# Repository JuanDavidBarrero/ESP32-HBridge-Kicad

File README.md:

# ESP32-HBridge-Kicad
 PCB EPS32 Hbridge

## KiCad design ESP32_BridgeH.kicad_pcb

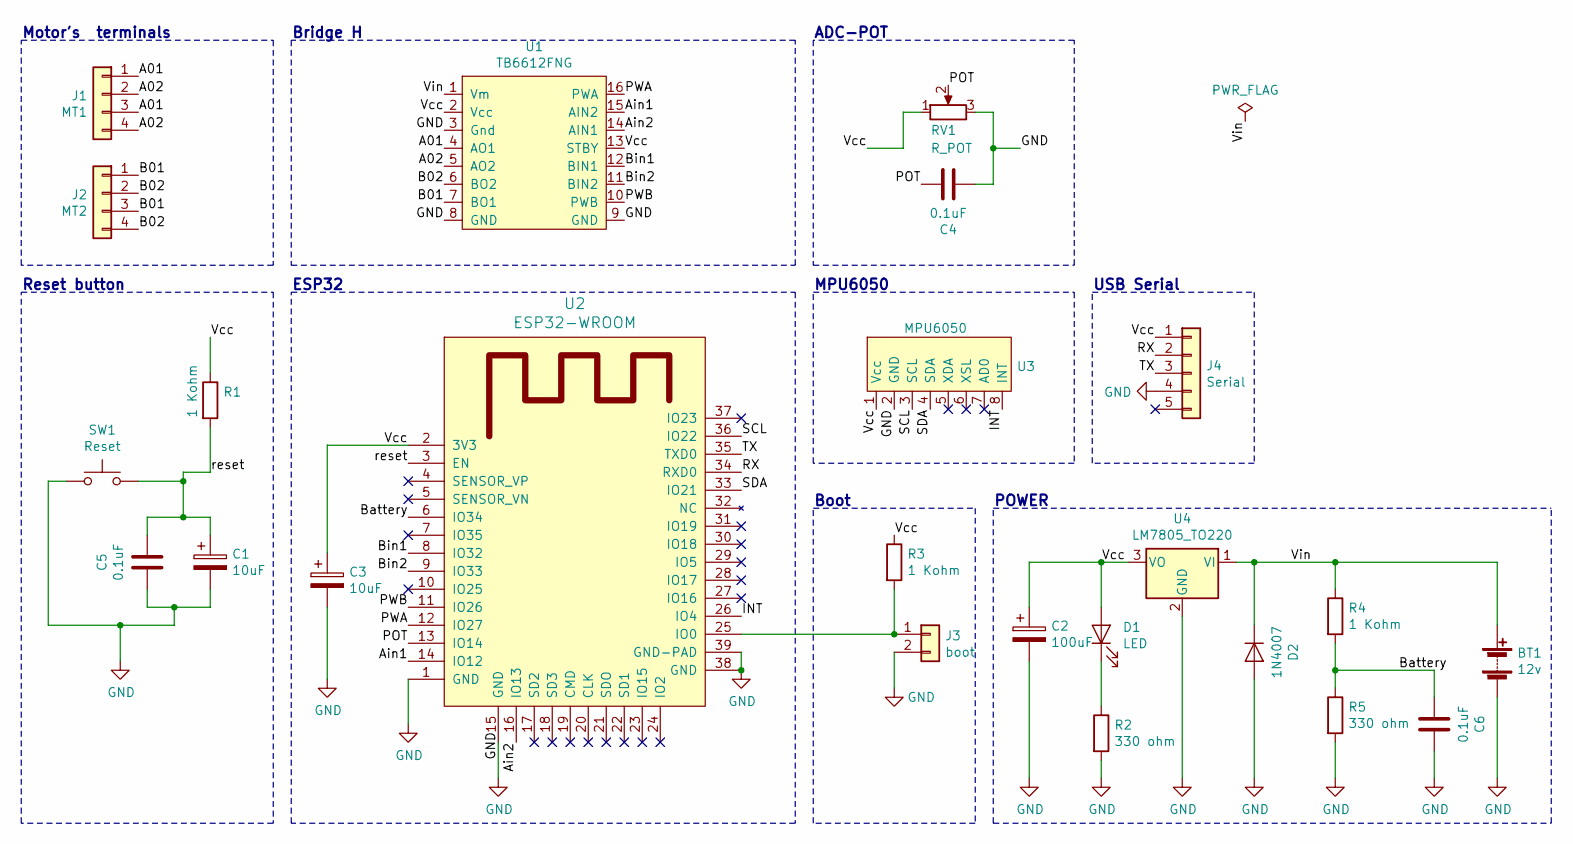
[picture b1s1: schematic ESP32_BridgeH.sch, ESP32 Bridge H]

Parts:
BT1: 12v; TerminalBlock_bornier-2_P5.08mm
C1, C3: 10uF; CP_Radial_D5.0mm_P2.50mm
C2: 100uF; CP_Radial_D8.0mm_P3.50mm
C4, C5, C6: 0.1uF; C_Disc_D4.3mm_W1.9mm_P5.00mm
D1: LED; LED_D5.0mm
D2: 1N4007; D_DO-41_SOD81_P10.16mm_Horizontal
J1: MT1; TerminalBlock_bornier-4_P5.08mm
J2: MT2; TerminalBlock_bornier-4_P5.08mm
J3: boot; PinHeader_1x02_P2.54mm_Vertical
J4: Serial; PinSocket_1x05_P2.54mm_Vertical
R1: 1 Kohm; R_Axial_DIN0207_L6.3mm_D2.5mm_P7.62mm_Horizontal
R2: 330 ohm; R_Axial_DIN0207_L6.3mm_D2.5mm_P7.62mm_Horizontal
R3, R4: 1 Kohm; R_Axial_DIN0207_L6.3mm_D2.5mm_P5.08mm_Vertical
R5: 330 ohm; R_Axial_DIN0207_L6.3mm_D2.5mm_P5.08mm_Vertical
RV1: R_POT; Potentiometer_Piher_T-16H_Single_Horizontal
SW1: Reset; SW_PUSH_6mm
U1: TB6612FNG
U2: ESP32-WROOM
U3: MPU6050; PinSocket_1x08_P2.54mm_Vertical
U4: LM7805_TO220; TO-220-3_Vertical

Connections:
/A01: J1.1, J1.3, U1.4 (AO1)
/A02: J1.2, J1.4, U1.5 (AO2)
/Ain1: U1.15 (AIN2), U2.14 (IO12)
/Ain2: U1.14 (AIN1), U2.16 (IO13)
/B01: J2.1, J2.3, U1.7 (BO1)
/B02: J2.2, J2.4, U1.6 (BO2)
/Battery: C6.1, R4.2, R5.1, U2.6 (IO34)
/Bin1: U1.12 (BIN1), U2.8 (IO32)
/Bin2: U1.11 (BIN2), U2.9 (IO33)
/INT: U2.26 (IO4), U3.8 (INT)
/POT: C4.2, RV1.2, U2.13 (IO14)
/PWA: U1.16 (PWA), U2.12 (IO27)
/PWB: U1.10 (PWB), U2.11 (IO26)
/RX: J4.2, U2.34 (RXD0)
/SCL: U2.36 (IO22), U3.3 (SCL)
/SDA: U2.33 (IO21), U3.4 (SDA)
/TX: J4.3, U2.35 (TXD0)
/Vcc: C2.1, C3.1, D1.2 (A), J4.1, R1.1, R3.1, RV1.1, U1.2 (Vcc), U1.13 (STBY), U2.2 (3V3), U3.1 (Vcc), U4.3 (VO)
/Vin: BT1.1 (+), D2.1 (K), R4.1, U1.1 (Vm), U4.1 (VI)
/reset: C1.1, C5.2, R1.2, SW1.2, U2.3 (EN)
GND: BT1.2 (-), C1.2, C2.2, C3.2, C4.1, C5.1, C6.2, D2.2 (A), J3.2, J4.4, R2.2, R5.2, RV1.3, SW1.1, U1.3 (Gnd), U1.8 (GND), U1.9 (GND), U2.1 (GND), U2.15 (GND), U2.38 (GND), U2.39 (GND-PAD), U3.2 (GND), U4.2 (GND)
unnamed: D1.1 (K), R2.1
unnamed: J3.1, R3.2, U2.25 (IO0)

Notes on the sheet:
Motor's terminals
Bridge H
Reset button
ESP32
POWER
ADC-POT
Boot
USB Serial
MPU6050

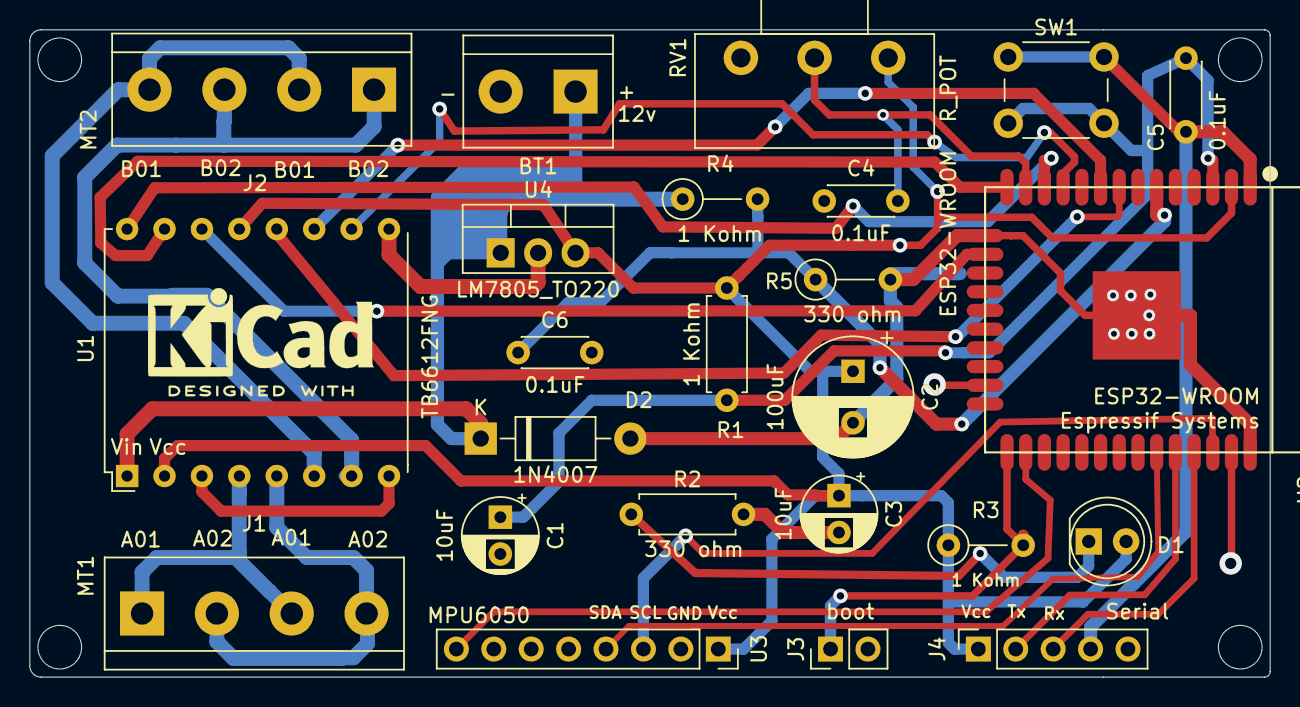
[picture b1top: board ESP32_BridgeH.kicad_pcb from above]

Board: 2 copper layers, 84.2 x 43.9 mm, 24 parts (0 on the bottom side), 23 nets.

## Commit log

2020-06-05 ESP32 H bridge V-1.0
2020-06-08 POT and aparallel diode
2020-06-08 foot-print assign to the new elements
2020-06-08 Net update and organizae components
2020-06-08 Routing
2020-06-09 Battery reader and boot correction
2020-06-09 new footprints without routing
2020-06-09 Routin v2.0 and kicadlogo
2020-06-14 JGB v2
2020-06-19 modification
2020-06-19 Lodo added v2.0
2020-07-11 fix button problem
2020-07-12 change regulator
